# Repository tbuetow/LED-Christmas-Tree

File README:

# 🎄RGB LED Christmas Trees!

Each year, I make a small holiday bauble for teachers, family, and friends. Usually my wife and I come up with an idea around Thanksgiving and then panic for three weeks to deliver something by the last day of school for the holidays.

This year we chose to revisit something we made 7 years ago, but improve on it, building on some of my more recent projects with addressable RGB LEDs and better tools like my multiple extruder 3D printer and solder reflow oven.

The concept is a clear thin 3D printed tree on top of a 3D printed base that powers LEDs inside of it. 7 years ago, this was a pair of AA batteries, a single discrete color changing LED, and a power switch. You could also run it off of a 5V supply via micro-USB. Times have changed now! I had a few simple improvements I wanted to make.

- USB-C with proper support for all USB-C power supplies. I chose to drop batteries just due to cost.
- A ring of addressable RGB LEDs instead of a single unmodifiable color changing LED.
- The ability to change the LED color effects, and provide many included options.
- Multiple color printing to make it more beautiful.
- Under $10 and very easy to manufacture, since we want to make 30-40 of these.
- Document the process to share with others and allow those who are inclined to write their one color effects.

## 3D Printed Parts
I designed the base and all other fixtures and accessories, except for the trees in Autodesk Fusion.

Printing was done on my Prusa XL and Core One.
I started by testing color combinations:

Once done, I was able to begin producing them multiples at a time:

The light dividers and trees were printed on the Core One. Lots of time starting the next print!

## Circuit Boards
The circuit boards were designed in KiCAD. Thanks to the power of modern microprocessors and addressable LEDs, the circuit is quite simple.

The control board is **very** small, just 37mm (under 1.5") across. This is in part because I can get the new(er) Microchip ATTiny1616 in a QFN packaged. These are ordered as bare PCBs and I use solder paste and stencils to set components and then reflow them in my solder oven. I would not recommend hand soldering these unless you are very skilled. It would be better to switch to slightly larger components and change the microprocessor out for one in a SOIC package or similar.

<Insert solder oven photo here>

## Software
I used PlatformIO in VSCode as my IDE to program the microcontrollers. This works well and makes it easy to import the Arduino framework and FastLED library for quick access to easy-to-use functions and tools.

The bulk of the code came from another project I made where I had LED name plates that were edge-lit with RGB LEDs. I just added a few additional effects. [main.cpp](src/main.cpp) is available in the [src](src/) folder.

# Building your own effects
## Prerequisites

## VSCode / PlatformIO

## Writing effects

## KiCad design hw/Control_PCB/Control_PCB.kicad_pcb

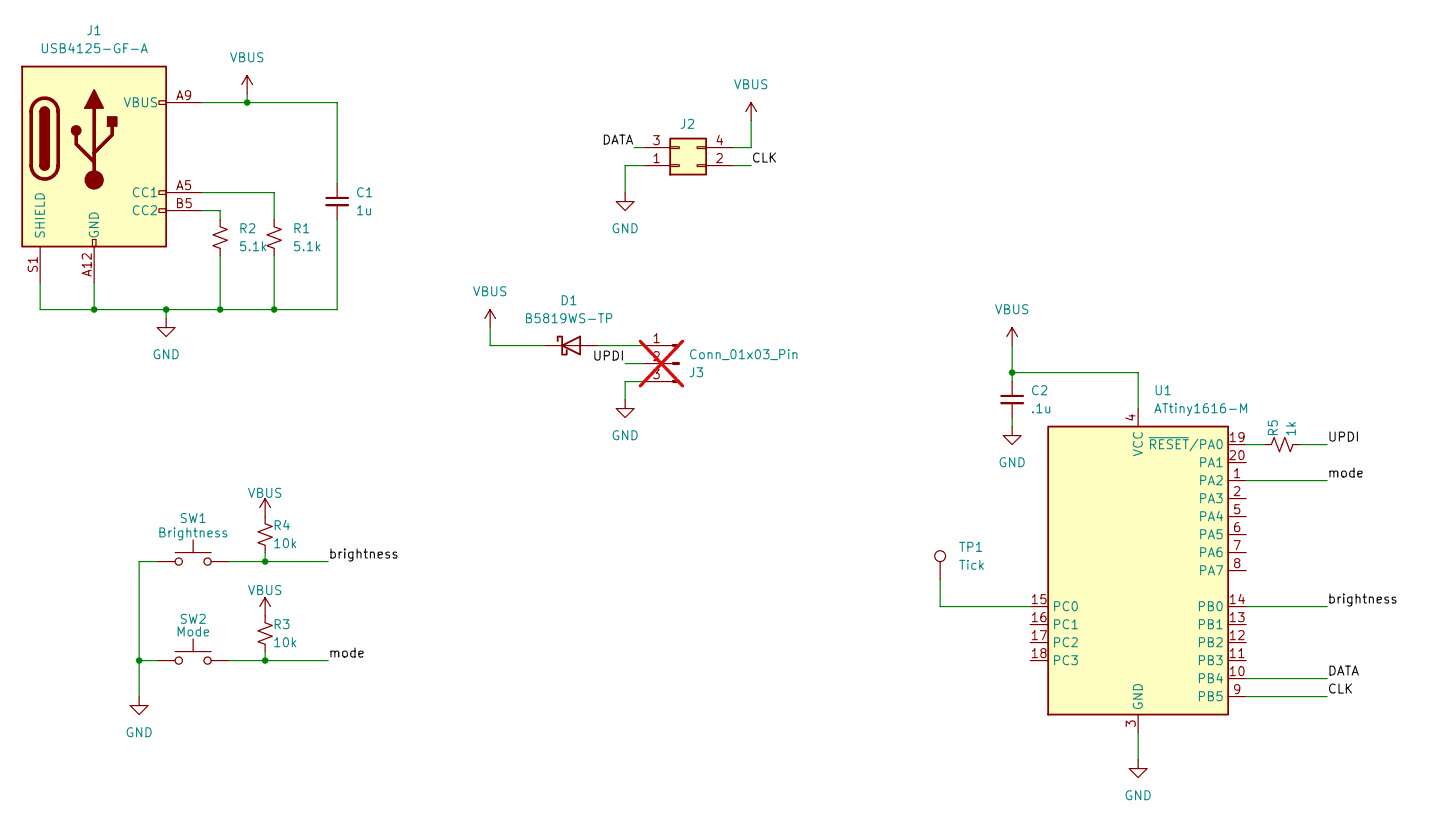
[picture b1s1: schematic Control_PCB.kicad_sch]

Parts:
C1: 1u; C_0603_1608Metric
C2: .1u; C_0603_1608Metric
D1: B5819WS-TP; D_SOD-323_HandSoldering
J1: USB4125-GF-A; USB_C_Receptacle_GCT_USB4125-xx-x_6P_TopMnt_Horizontal
J2: PRPC040DAAN-RC; PinHeader_2x02_P2.54mm_Vertical
J3: Conn_01x03_Pin; PinHeader_1x03_P2.54mm_Vertical; not fitted
R1, R2: 5.1k; R_0603_1608Metric
R3, R4: 10k; R_0603_1608Metric
R5: 1k; R_0603_1608Metric
SW1: Brightness; SW_SPST_EVQP7C
SW2: Mode; SW_SPST_EVQP7C
TP1: Tick; TestPoint_Pad_D1.0mm
U1: ATtiny1616-M; VQFN-20-1EP_3x3mm_P0.4mm_EP1.7x1.7mm

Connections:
/CLK: J2.2, U1.9 (PB5)
/DATA: J2.3, U1.10 (PB4)
/UPDI: J3.2, R5.2
/brightness: R4.2, SW1.2, U1.14 (PB0)
/mode: R3.2, SW2.2, U1.1 (PA2)
GND: C1.2, C2.2, J1.A12 (GND), J1.B12 (GND), J1.S1 (SHIELD), J2.1, J3.3, R1.2, R2.2, SW1.1, SW2.1, U1.3 (GND), U1.21 (GND)
unnamed: D1.2 (A), J3.1
unnamed: J1.A5 (CC1), R1.1
unnamed: J1.B5 (CC2), R2.1
unnamed: TP1.1, U1.15 (PC0)
unnamed: R5.1, U1.19 (~RESET/PA0)
VBUS: C1.1, C2.1, D1.1 (K), J1.A9 (VBUS), J1.B9 (VBUS), J2.4, R3.1, R4.1, U1.4 (VCC)

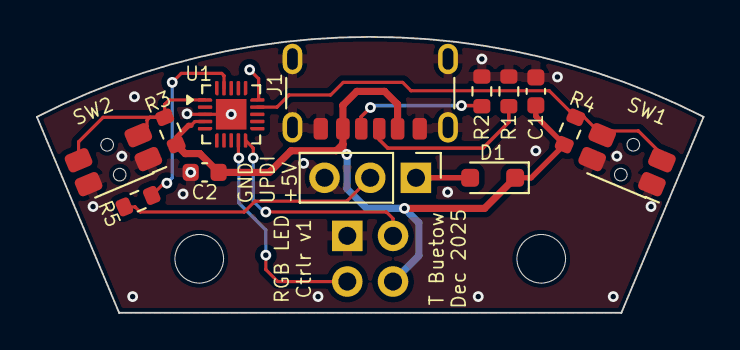
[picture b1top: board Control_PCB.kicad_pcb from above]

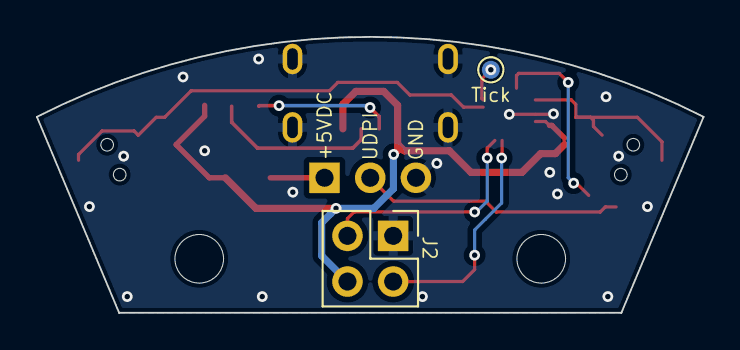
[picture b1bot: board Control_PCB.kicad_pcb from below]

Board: 2 copper layers, 37.0 x 15.3 mm, 15 parts (2 on the bottom side), 12 nets.

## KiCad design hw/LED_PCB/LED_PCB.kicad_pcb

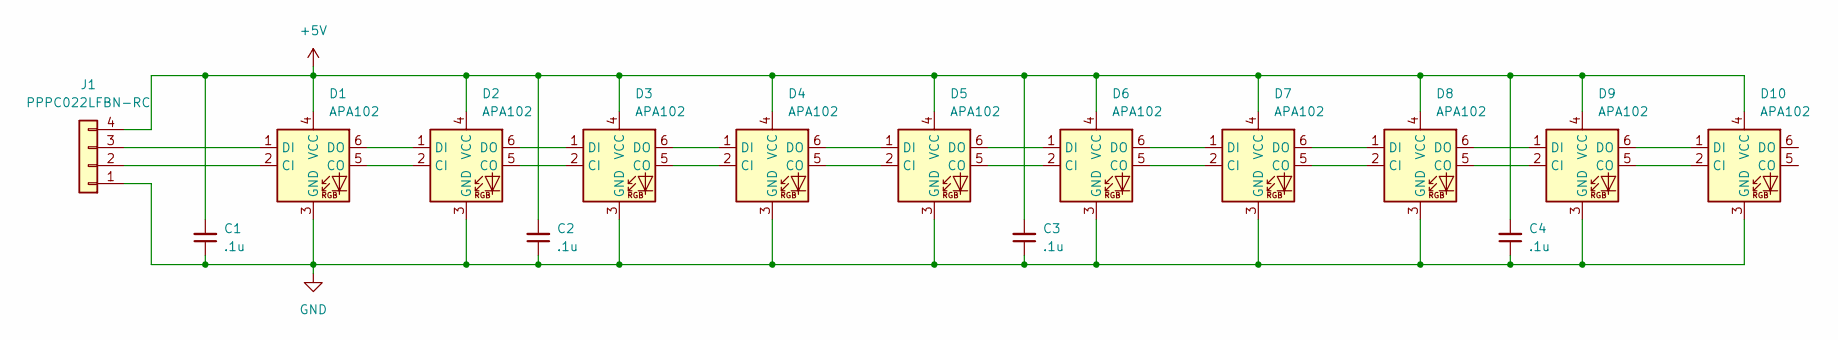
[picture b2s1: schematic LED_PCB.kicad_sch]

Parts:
C1, C2, C3, C4: .1u; C_0603_1608Metric
D1, D2, D3, D4, D5, D6, D7, D8, D9, D10: APA102; LED_RGB_5050-6
J1: PPPC022LFBN-RC; PinSocket_2x02_P2.54mm_Vertical

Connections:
+5V: C1.2, C2.2, C3.2, C4.2, D1.4 (VCC), D2.4 (VCC), D3.4 (VCC), D4.4 (VCC), D5.4 (VCC), D6.4 (VCC), D7.4 (VCC), D8.4 (VCC), D9.4 (VCC), D10.4 (VCC), J1.4
GND: C1.1, C2.1, C3.1, C4.1, D1.3 (GND), D2.3 (GND), D3.3 (GND), D4.3 (GND), D5.3 (GND), D6.3 (GND), D7.3 (GND), D8.3 (GND), D9.3 (GND), D10.3 (GND), J1.1
unnamed: D1.2 (CI), J1.2
unnamed: D1.5 (CO), D2.2 (CI)
unnamed: D1.1 (DI), J1.3
unnamed: D1.6 (DO), D2.1 (DI)
unnamed: D2.5 (CO), D3.2 (CI)
unnamed: D2.6 (DO), D3.1 (DI)
unnamed: D3.5 (CO), D4.2 (CI)
unnamed: D3.6 (DO), D4.1 (DI)
unnamed: D4.5 (CO), D5.2 (CI)
unnamed: D4.6 (DO), D5.1 (DI)
unnamed: D5.5 (CO), D6.2 (CI)
unnamed: D5.6 (DO), D6.1 (DI)
unnamed: D6.5 (CO), D7.2 (CI)
unnamed: D6.6 (DO), D7.1 (DI)
unnamed: D7.5 (CO), D8.2 (CI)
unnamed: D7.6 (DO), D8.1 (DI)
unnamed: D8.5 (CO), D9.2 (CI)
unnamed: D8.6 (DO), D9.1 (DI)
unnamed: D9.5 (CO), D10.2 (CI)
unnamed: D9.6 (DO), D10.1 (DI)

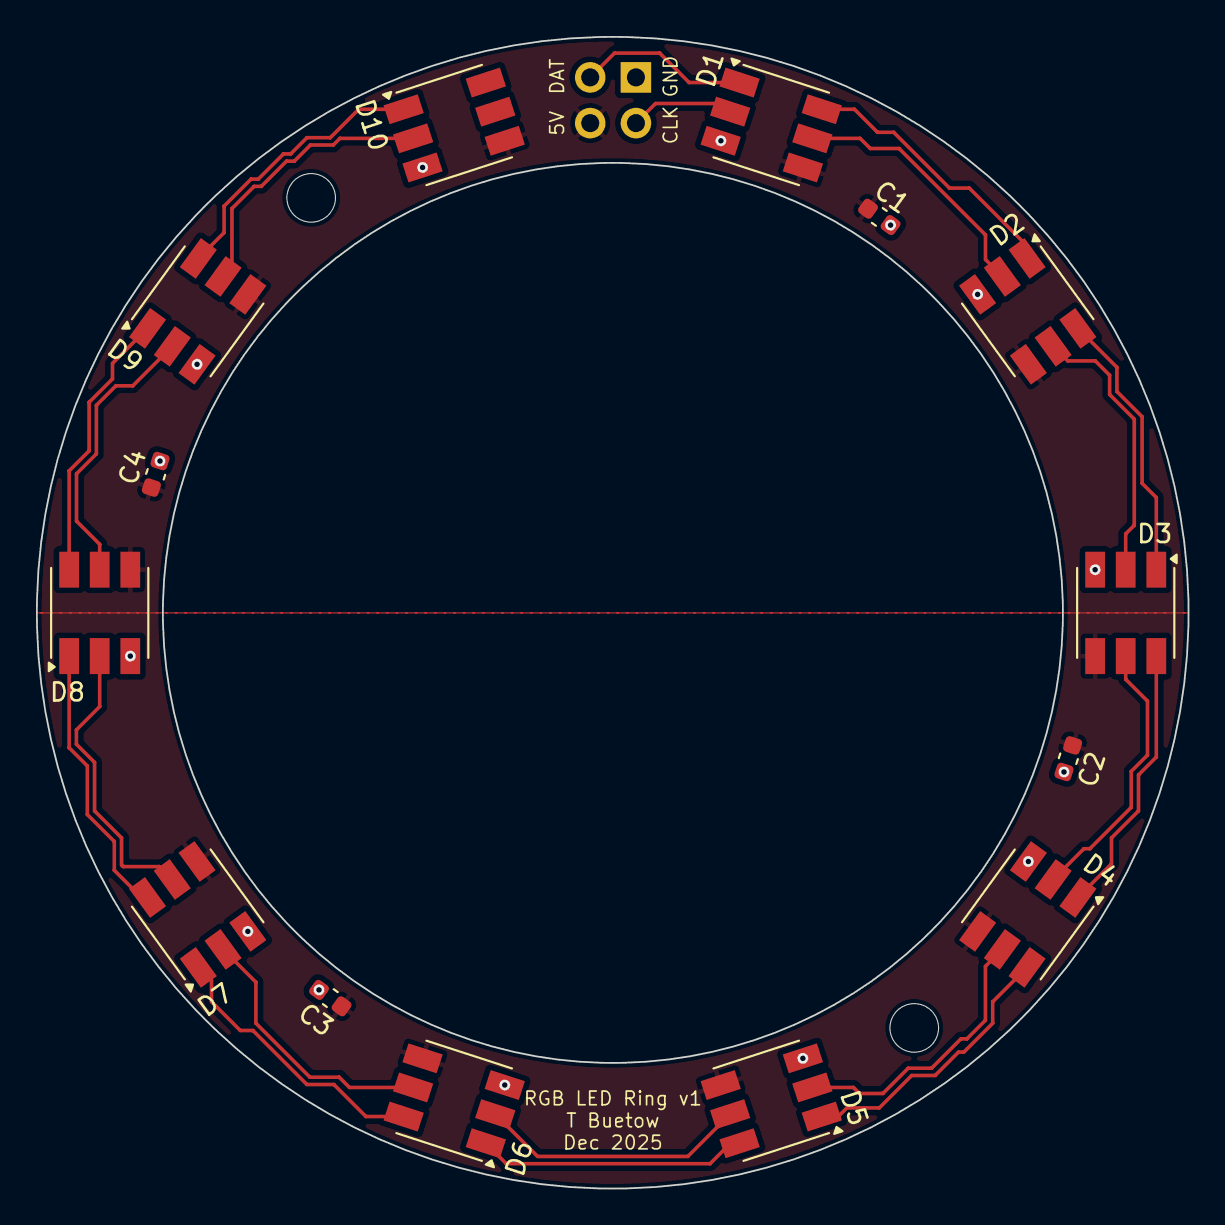
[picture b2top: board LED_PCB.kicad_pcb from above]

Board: 2 copper layers, 64.0 x 64.0 mm, 15 parts (1 on the bottom side), 22 nets.

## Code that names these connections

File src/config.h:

#pragma once
#include <stdint.h>
#include <FastLED.h>

namespace Config {

// PATTERN CONTROL //
//Rainbow Cycles
constexpr uint16_t CYCLE_TIME_SECONDS_SLOW = 300; 
constexpr uint8_t CYCLE_TIME_SECONDS_FAST = 10; //also used for rainbow wave

//Parade Cycles
constexpr uint8_t PARADE_CYCLE_TIME_SECONDS = 2;

//Twinkles
constexpr uint16_t TWINKLE_RISE_TIME_MS = 75;
constexpr uint16_t TWINKLE_FALL_TIME_MS = 1300;
constexpr uint16_t TWINKLE_REST_TIME_MS = 1500;
constexpr uint8_t TWINKLE_CHANCE = 1; // percent chance every cycle time

//Noise
constexpr uint8_t BLEND_DISTANCE = 50; // value 0 - 127 from which to stop blending in white and become solid.
constexpr uint8_t NOISE_SAMPLE_DISTANCE = 40; // "distance" between each LED on the 1-D noise map. Farther distances make each LED more independent.
constexpr uint8_t NOISE_Z_STEP = 2; // "time" axis to move perlin noise in 2D map with each step. Larger steps make the pattern move faster.

//Solid colors
constexpr uint8_t GREEN_HUE = 97; // Green - scaled to 0..255 instead of 0..360deg
constexpr uint8_t RED_HUE = 0; // Red - scaled to 0..255 instead of 0..360deg


// HARDWARE CONFIG //
constexpr uint8_t DATA_PIN = PIN_PB4;          // Physical PB4
constexpr uint8_t CLK_PIN = PIN_PB5;           // Physical PB5
constexpr uint8_t TICK_OUT_BIT = PIN0_bp;      // Physical PC0, accessed through VPORTC
constexpr uint8_t BRIGHTNESS_BUTTON_BIT = PIN0_bp; // Physical PB0
constexpr uint8_t MODE_BUTTON_BIT = PIN2_bp;        // Physical PA2
constexpr uint8_t NUM_LEDS = 10; //Number of LEDS on the board
constexpr fl::EOrder LED_COLOR_ORDER = BGR; //RBG usually for adafruit, BGR usually for Aliexpress vendor COCurve 
constexpr uint8_t EEPROM_ADDR_BRIGHTNESS = 0x01;
constexpr uint8_t EEPROM_ADDR_MODE = 0x02;


// BRIGHTNESS and MODES //
constexpr uint8_t BRIGHTNESS_STEPS = 4; //Number of steps to divide min 50 and max 255 into.
constexpr uint8_t BUTTON_SAMPLE_MS = 10;


} // namespace Config

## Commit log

2025-12-07 Initial hardware designs. PCBs ready for final review.
2025-12-08 Init platform.io
2025-12-09 Add fastled library. Import RGB name tag code from attiny85. Will need to be ported to attiny 1 series
2025-12-09 PCB release to manufacturing
2025-12-09 BOM complete
2025-12-13 Base ready to begin printing
2025-12-13 Created complete BOM
2025-12-13 Tree files and projects with README and licenses.
2025-12-13 Add clamp to solder fixture
2025-12-13 Start of readme
2025-12-14 Update README some more. Remove stock PIO lib and include folders.
2025-12-14 Fix readme extension for github. Fix images, no heic allowed.
2025-12-14 Rename README to README.md
2025-12-14 More readme updates. Embedded Fusion viewer. Prerequisites for dev.
2025-12-14 No iframes in github markdown. Removed.
2025-12-15 Code compiles! Unable to test on hardware yet.
2025-12-15 Remove some static effects, excise remaining #define, config at top for LED color order.
2025-12-15 Cleaning up main.cpp. Just need to do the effects now.
2025-12-16 Now has output but still not as expected.
2025-12-17 Remove APA102HD - does not work with ATtiny1616 for some reason.
2025-12-17 Reworked timers, button servicing. Reduce files - move input (just button servicing) to hardware.
2025-12-17 Add cpp compiler version, force serial updi (jtag is default and doens't work)
2025-12-17 debugging images of oscope
2025-12-17 Projection changes based on trying to install buttons.
2025-12-17 Change UPDI buffer resistor to 0 Ohms. Internet recommendation of 1k didn't work. Not sure this is needed because of diode on UPDI 5V rail.
2025-12-17 Update solder screen fixture based on first useage. Make it easier to remove boards.
2025-12-18 Rainbow, solids, and parade working. Need to make twinkling better. Need to add carousel - after I define what I want it to look like. Set proper green and red hues.
2025-12-19 New effects largely in place. Still need to tune perlin noise and twinkling.
2025-12-19 More twinkle tuning. Added rest timer.
2025-12-19 noise blending better. Issue with red flickering still to solve.
2025-12-19 Working noise! All parameters tuned enough to make me happy.
2025-12-19 Further manufacturing updates - 3mf projects now contain latest version of base.
2025-12-19 Update label with correct effects. Add under construction to README.
2025-12-19 Much better understanding of perlin noise - added adjustable 1D distance parameter.
2025-12-19 Smarter solid fills, like the solid rainbow.
2025-12-23 Major update to readme - all build info complete.
2025-12-24 Proofreading and filling out missing section on setting up VS Code.
2025-12-28 Update shared Fusion model. More details to note on how to edit text.
